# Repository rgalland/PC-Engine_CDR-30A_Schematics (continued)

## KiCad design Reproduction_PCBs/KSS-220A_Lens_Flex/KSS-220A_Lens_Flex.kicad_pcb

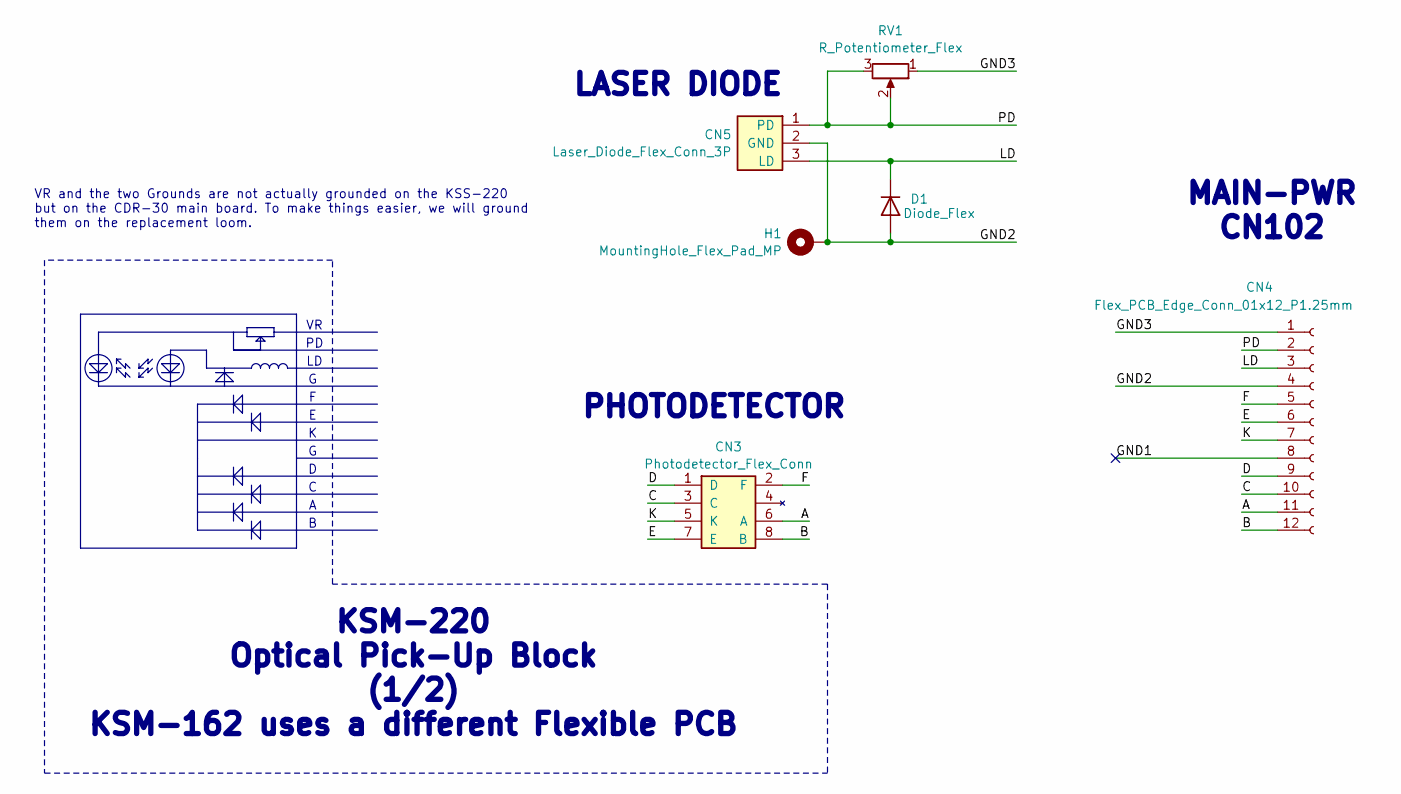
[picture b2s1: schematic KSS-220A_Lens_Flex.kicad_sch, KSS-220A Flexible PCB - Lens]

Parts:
CN3: Photodetector_Flex_Conn; FLEX_SOIC-LIKE_8_3.9x4.9mm_P1.27mm
CN4: Flex_PCB_Edge_Conn_01x12_P1.25mm; Flexible_PCB_Conn_1x12_P1.25mm
CN5: Laser_Diode_Flex_Conn_3P; Laser_Diode_Pads
D1: Diode_Flex; Diode_Flex_Pads
H1: MountingHole_Flex_Pad_MP; MountingHole_1.6mm_Pad
RV1: R_Potentiometer_Flex; Potentiometer_Flex_Pads

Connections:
/A: CN3.6 (A), CN4.11
/B: CN3.8 (B), CN4.12
/C: CN3.3 (C), CN4.10
/D: CN3.1 (D), CN4.9
/E: CN3.7 (E), CN4.6
/F: CN3.2 (F), CN4.5
/GND1: CN4.8
/GND2: CN4.4, CN5.2 (GND), D1.2 (A), H1.MP
/GND3: CN4.1, RV1.1
/K: CN3.5 (K), CN4.7
/LD: CN4.3, CN5.3 (LD), D1.1 (K)
/PD: CN4.2, CN5.1 (PD), RV1.2, RV1.3

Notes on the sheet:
PHOTODETECTOR
KSM-220 Optical Pick-Up Block (1/2) KSM-162 uses a different Flexible PCB
LASER DIODE
MAIN-PWR CN102
VR and the two Grounds are not actually grounded on the KSS-220 but on the CDR-30 main board. To make things easier, we will ground them on the replacement loom.

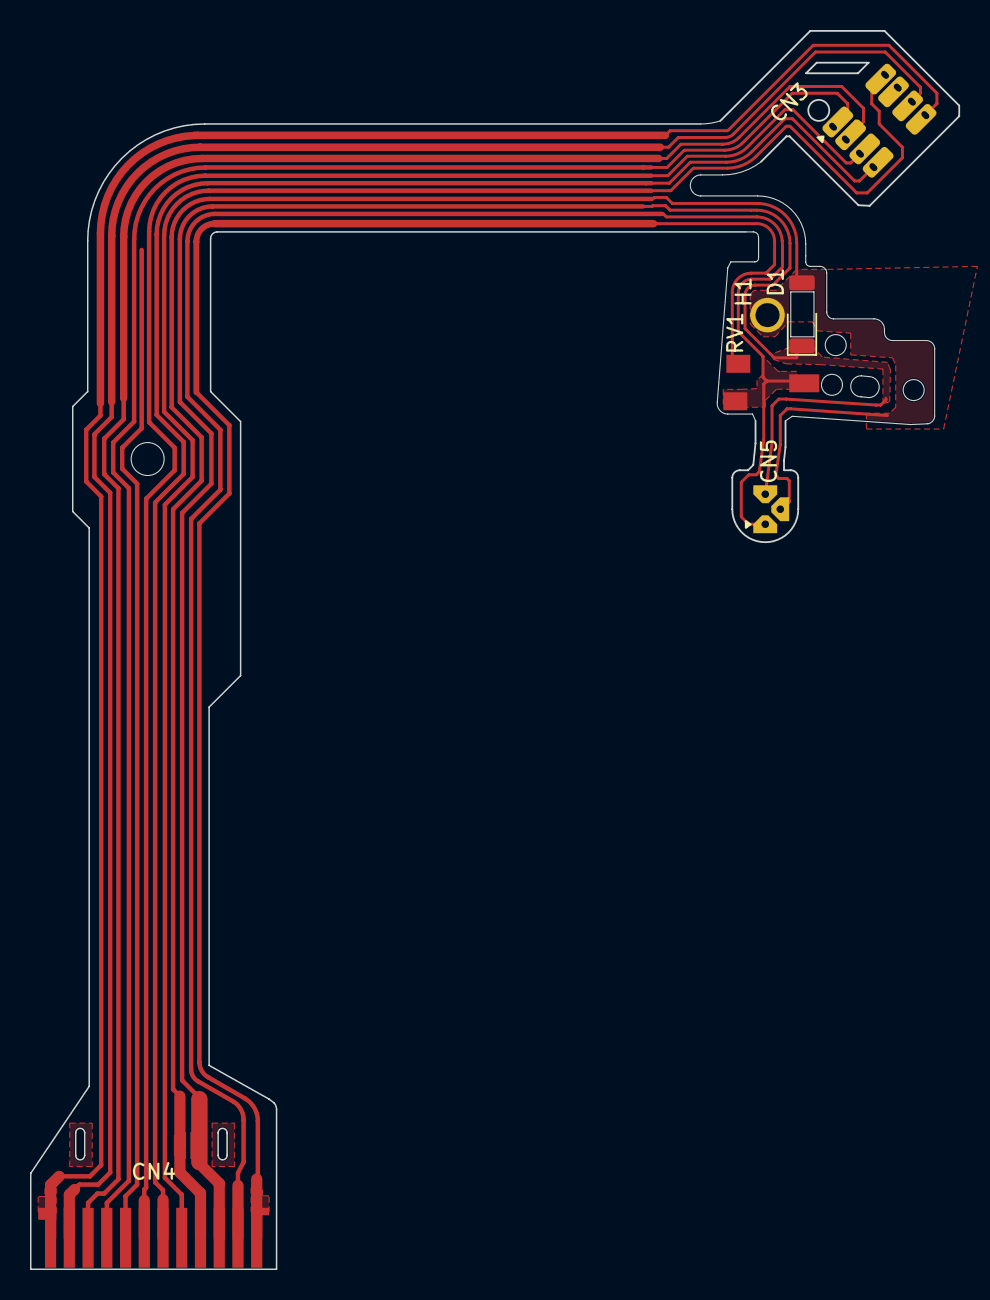
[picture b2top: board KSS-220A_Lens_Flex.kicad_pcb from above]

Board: 2 copper layers, 61.9 x 82.6 mm, 6 parts (0 on the bottom side), 11 nets.

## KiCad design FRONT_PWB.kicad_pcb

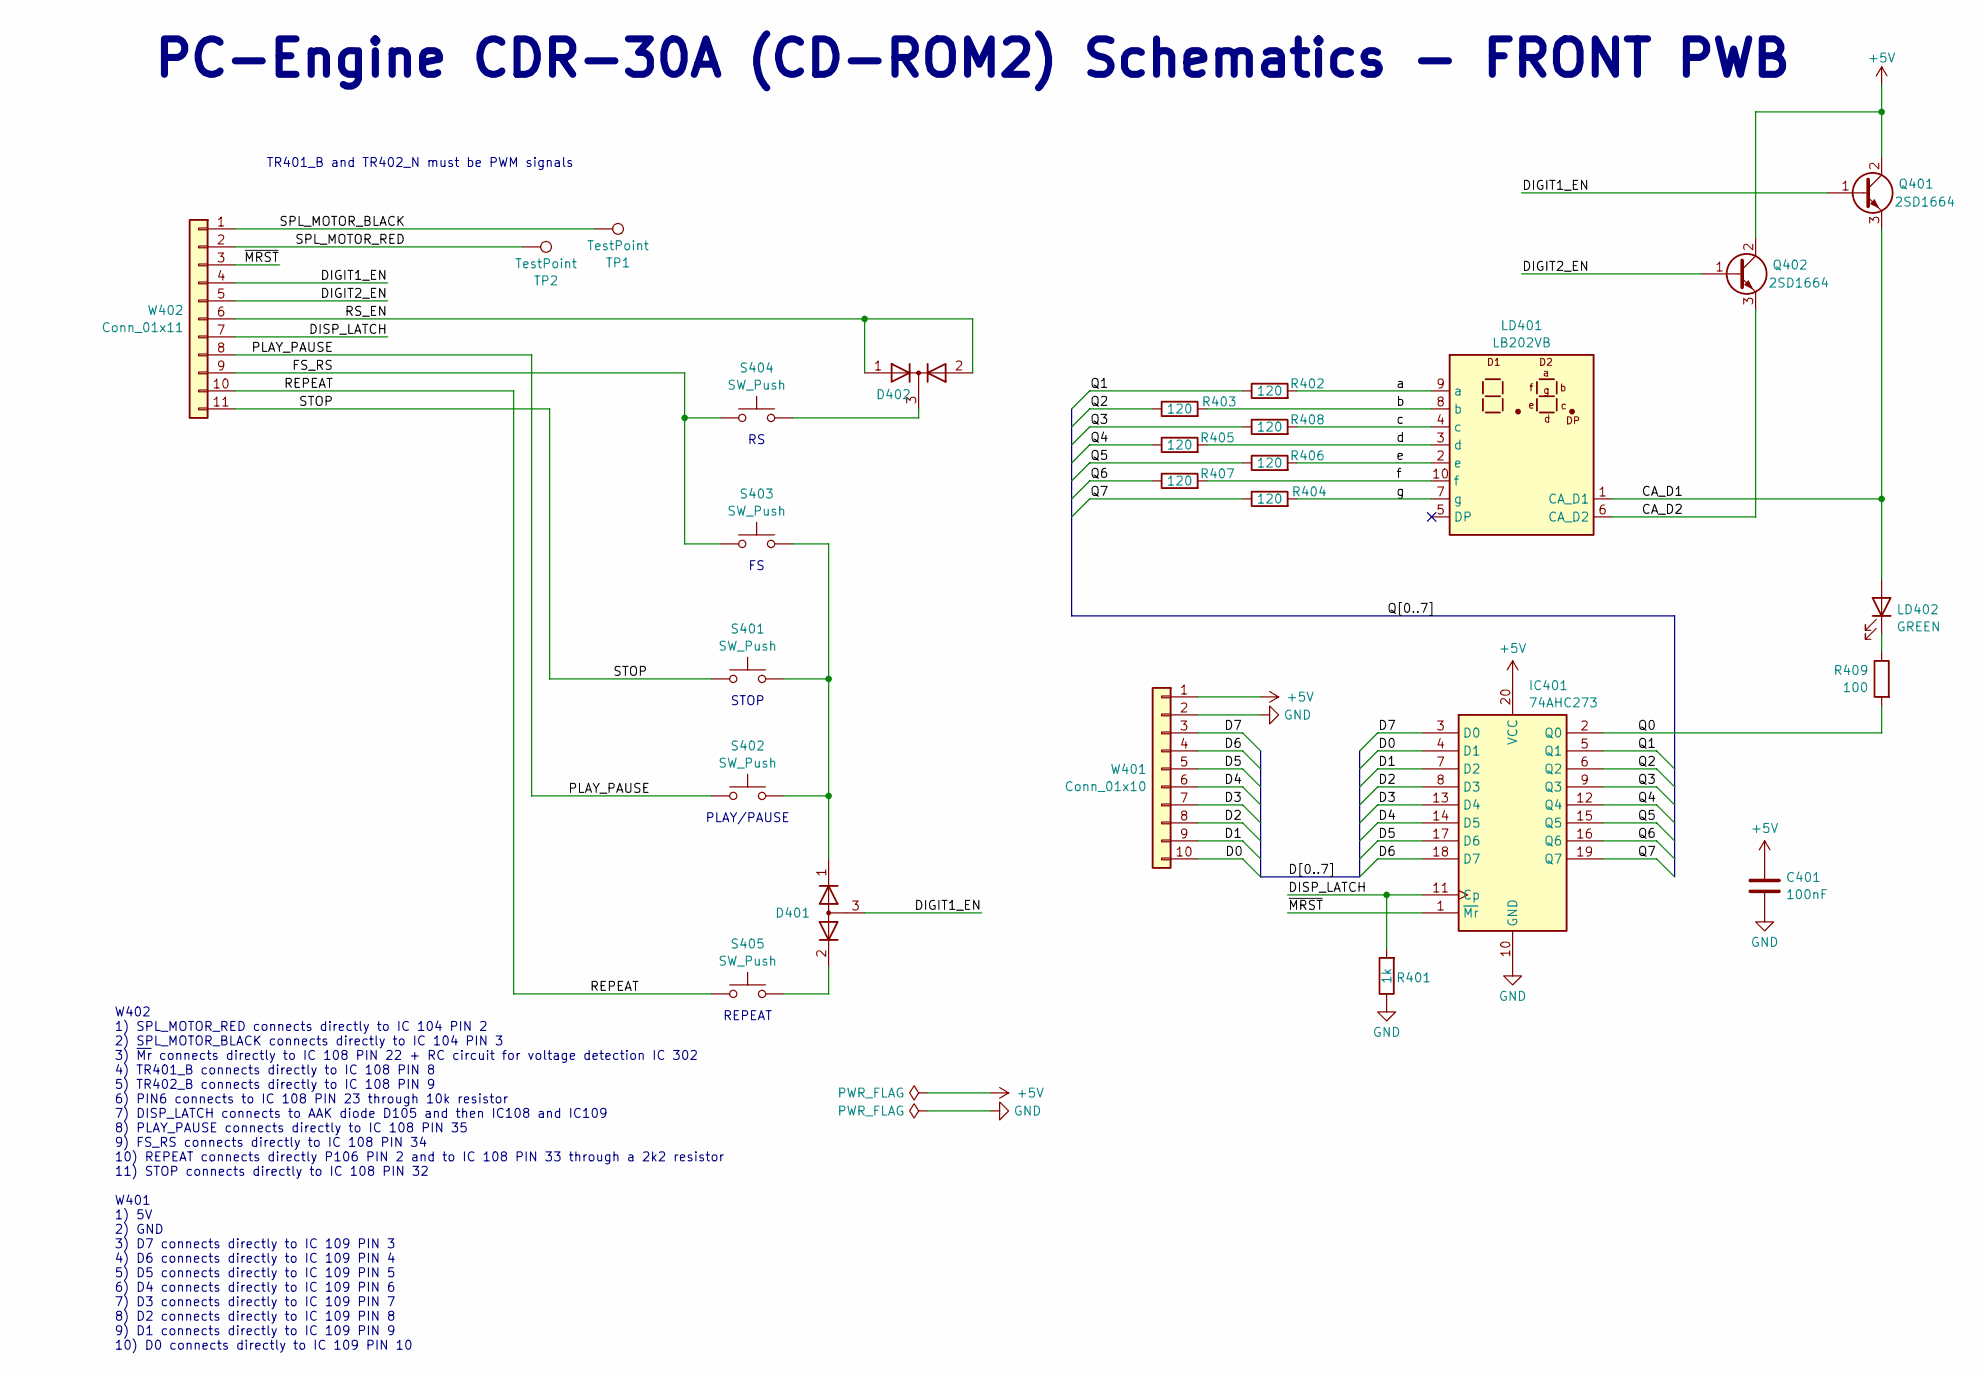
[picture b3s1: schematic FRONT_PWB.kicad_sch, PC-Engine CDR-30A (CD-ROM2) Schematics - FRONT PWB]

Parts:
C401: 100nF; C_0805_2012Metric
D401: D_Zener_Dual_CommonAnode_KKA; SOT-23
D402: D_Dual_CommonCathode_AAK; SOT-23
IC401: 74AHC273; SOIC-20W_7.5x12.8mm_P1.27mm
LD401: LB202VB; ELD_426XXXX
LD402: GREEN; LED_D3.0mm
Q401, Q402: 2SD1664; SOT-89-3
R401: 1k; R_0805_2012Metric
R402, R403, R404, R405, R406, R407, R408: 120; R_0805_2012Metric
R409: 100; R_0805_2012Metric
S401, S402, S403, S404, S405: SW_Push; SW_PUSH_6mm_H4.3mm
TP1, TP2: TestPoint; TestPoint_Pad_D3.0mm
W401: Conn_01x10; JST_ZE_B10B-ZESK-1D_1x10_P1.50mm_Vertical
W402: Conn_01x11; JST_ZE_B11B-ZESK-1D_1x11_P1.50mm_Vertical

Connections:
+5V: C401.1, IC401.20 (VCC), Q401.2 (C), Q402.2 (C), W401.1
/CA_D1: LD401.1 (CA_D1), LD402.2 (A), Q401.3 (E)
/CA_D2: LD401.6 (CA_D2), Q402.3 (E)
/D0: IC401.4 (D1), W401.10
/D1: IC401.7 (D2), W401.9
/D2: IC401.8 (D3), W401.8
/D3: IC401.13 (D4), W401.7
/D4: IC401.14 (D5), W401.6
/D5: IC401.17 (D6), W401.5
/D6: IC401.18 (D7), W401.4
/D7: IC401.3 (D0), W401.3
/DISP_LATCH: IC401.11 (Cp), R401.2, W402.7
/FS_RS: S403.2, S404.2, W402.9
/PLAY_PAUSE: S402.1, W402.8
/Q0: IC401.2 (Q0), R409.2
/Q1: IC401.5 (Q1), R402.1
/Q2: IC401.6 (Q2), R403.1
/Q3: IC401.9 (Q3), R408.1
/Q4: IC401.12 (Q4), R405.1
/Q5: IC401.15 (Q5), R406.1
/Q6: IC401.16 (Q6), R407.1
/Q7: IC401.19 (Q7), R404.1
/REPEAT: S405.2, W402.10
/SPL_MOTOR_BLACK: TP1.1, W402.1
/SPL_MOTOR_RED: TP2.1, W402.2
/STOP: S401.1, W402.11
/TR401_B: D401.3 (A), Q401.1 (B), W402.4
/TR402_B: Q402.1 (B), W402.5
/a: LD401.9 (a), R402.2
/b: LD401.8 (b), R403.2
/c: LD401.4 (c), R408.2
/d: LD401.3 (d), R405.2
/e: LD401.2 (e), R406.2
/f: LD401.10 (f), R407.2
/g: LD401.7 (g), R404.2
/~Mr: IC401.1 (~Mr), W402.3
GND: C401.2, IC401.10 (GND), R401.1, W401.2
unnamed: D401.1 (K), S401.2, S402.2, S403.1
unnamed: D401.2 (K), S405.1
unnamed: D402.3 (K), S404.1
unnamed: LD402.1 (K), R409.1
unnamed: D402.1 (A), D402.2 (A), W402.6

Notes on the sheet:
TR401_B and TR402_N must be PWM signals
STOP
W402 1) SPL_MOTOR_RED connects directly to IC 104 PIN 2 2) SPL_MOTOR_BLACK connects directly to IC 104 PIN 3 3) ~{Mr} connects directly to IC 108 PIN 22 + RC circuit for voltage detection IC 302 4) TR401_B connects directly to IC 108 PIN 8 5) TR402_B connects directly to IC 108 PIN 9 6) PIN6 connec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
REPEAT
PLAY/PAUSE
PC-Engine CDR-30A (CD-ROM2) Schematics - FRONT PWB

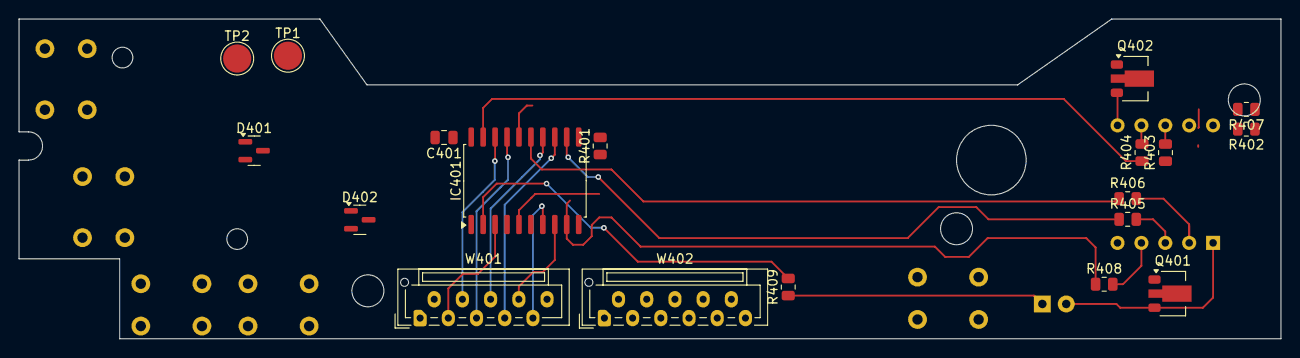
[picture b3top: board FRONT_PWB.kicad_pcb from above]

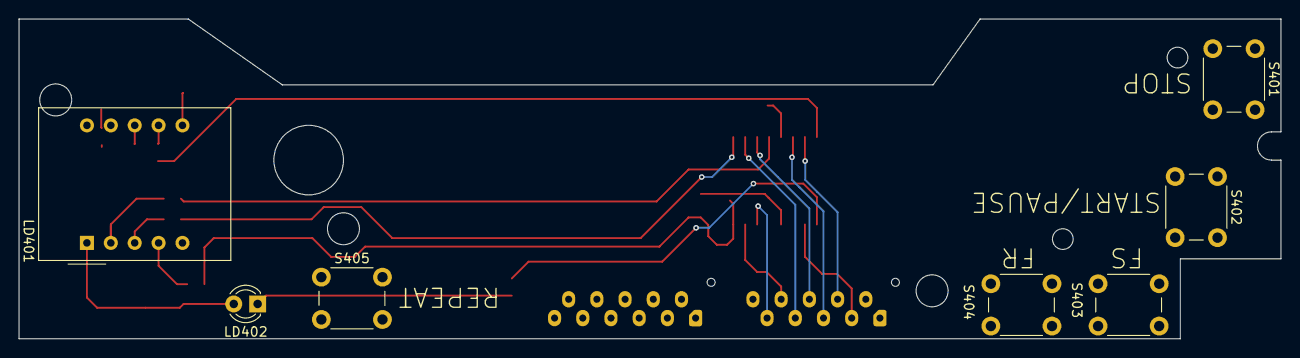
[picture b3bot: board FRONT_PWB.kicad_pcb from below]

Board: 2 copper layers, 134.2 x 34.0 mm, 26 parts (7 on the bottom side), 42 nets.

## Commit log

2024-05-11 Note added about DSP + external RAM also found in some CDR-30As. .gitattributes files added
2024-07-19 Small Schematics update to tidy signals attached to SCSI and MCU chips.
2024-07-30 Small update, some typo fixes, more comments added to help understanding
2024-08-16 KSS-220A Flexible PCBs ready and on order for trial.
2025-02-09 New structure for all PCBs related to NEC CDR-30A (PCE CD-ROM2)
2025-02-24 Lib update
2025-02-24 Subdirectory added as submodule by mistake.
2025-02-24 Final fixes to include some ectra mounting holes + GND connection to shield
2025-02-26 Final commit before ordering
2025-02-26 Readme updated to list versions
